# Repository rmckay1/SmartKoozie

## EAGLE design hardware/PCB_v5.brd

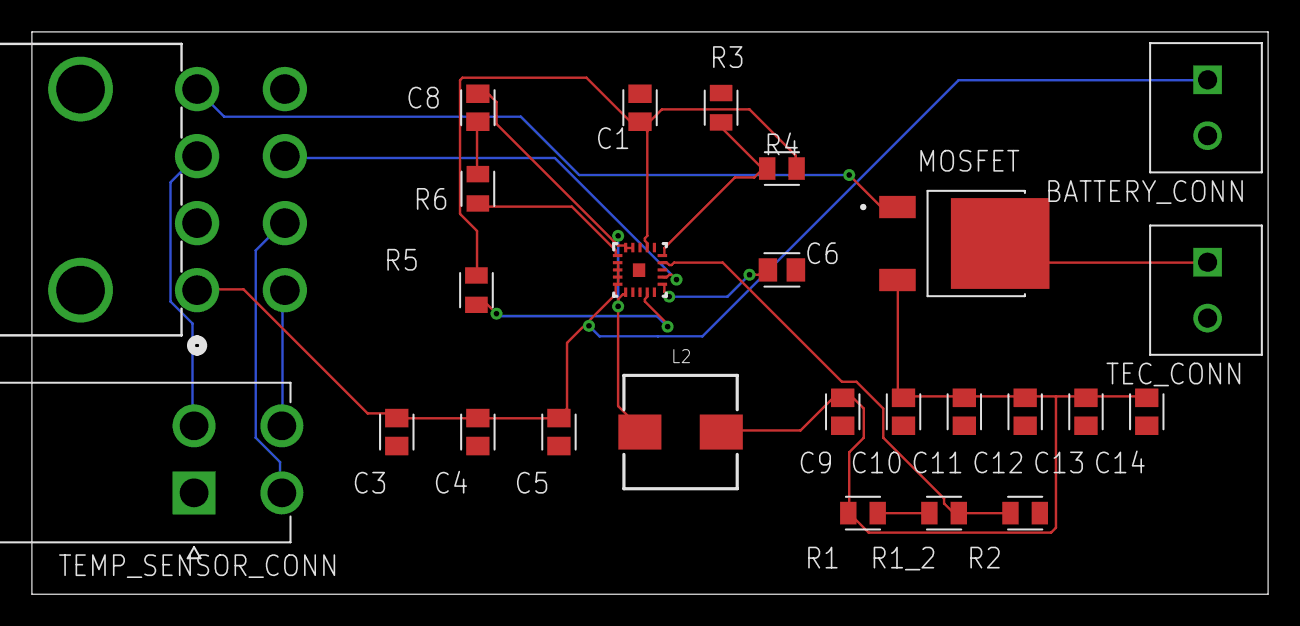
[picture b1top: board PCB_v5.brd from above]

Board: 2 copper layers, 77.4 x 35.2 mm, 26 parts (0 on the bottom side), 18 nets.

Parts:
ARDUINO_CONN: 39301080CONN_5569-08A_MOL; CONN_5569-08A_MOL
BATTERY_CONN: OSTTE020104; OST_OSTTE020104
BUCK_CONVERTER: TPS568230RJERRJE0020A; RJE0020A
C1: 1µF; CAPC2012X110
C3, C4, C10, C11, C12, C13, C14: 22µF; CAPC2012X110
C5, C8, C9: 0.1µF; CAPC2012X110
C6: 22nF; CAPC2012X110
L2: 1.5uF; WE-HCI_7050
MOSFET: TSM340N06CP_ROG; TRANS_TSM340N06CP_ROG
R1: 280k; RESC2012X65
R1_2: 10k; RESC2012X65
R2: 30k; RESC2012X65
R3: 5.1k; RESC2012X65
R4: 330k; RESC2012X65
R5: 100K; RESC2012X65
R6: 0; RESC2012X65
TEC_CONN: OSTTE020104; OST_OSTTE020104
TEMP_SENSOR_CONN: 353180420; MOLEX_353180420

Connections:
5V: ARDUINO_CONN.3, TEMP_SENSOR_CONN.2
COOLER_PWR: MOSFET.2, TEC_CONN.1
EN: ARDUINO_CONN.7, BUCK_CONVERTER.12
GND: ARDUINO_CONN.2, BATTERY_CONN.2, BUCK_CONVERTER.7, BUCK_CONVERTER.8, BUCK_CONVERTER.10, BUCK_CONVERTER.13, BUCK_CONVERTER.16, BUCK_CONVERTER.18, BUCK_CONVERTER.21, C1.2, C3.1, C4.1, C5.1, C6.2, C9.1, C10.1, C11.1, C12.1, C13.1, C14.1, R2.2, R3.1, TEC_CONN.2, TEMP_SENSOR_CONN.1
MODE: BUCK_CONVERTER.15, R3.2, R4.2
unnamed: BUCK_CONVERTER.9, R5.2
unnamed: BUCK_CONVERTER.11, C6.1
unnamed: BUCK_CONVERTER.1, R6.1
unnamed: C8.2, R6.2
unnamed: BUCK_CONVERTER.14, R1_2.2, R2.1
unnamed: R1.2, R1_2.1
PWM: ARDUINO_CONN.4, MOSFET.1
SCL: ARDUINO_CONN.5, TEMP_SENSOR_CONN.4
SDA: ARDUINO_CONN.6, TEMP_SENSOR_CONN.3
SW: BUCK_CONVERTER.6, BUCK_CONVERTER.19, BUCK_CONVERTER.20, C8.1, L2.1
VCC: BUCK_CONVERTER.17, C1.1, R4.1, R5.1
VIN: ARDUINO_CONN.1, BATTERY_CONN.1, BUCK_CONVERTER.2, BUCK_CONVERTER.3, BUCK_CONVERTER.4, BUCK_CONVERTER.5, C3.2, C4.2, C5.2
VOUT: C9.2, C10.2, C11.2, C12.2, C13.2, C14.2, L2.2, MOSFET.3, R1.1

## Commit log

2025-02-25 Setup
2025-03-13 Create Order Receipts
2025-03-13 added a picture of ordered parts in the hardware folder
2025-03-13 add receipts directory
2025-03-16 Added website folder and website draft
2025-04-02 Starting file of our schematic, created the pins for the Nano
2025-04-02 Created Part forlder for the scheamtic
2025-04-03 created symbol for the mosfet and added it to the schematic
2025-04-03 added the open pins in the schematic for the buck converter
2025-04-08 Removed embedded repo SmartKoozieApp and ignored it
2025-04-08 Moved show_temp folder into firmware
2025-04-08 Moved RemoteXY_V1 folder to firmware folder
2025-04-08 Moved TempSensor folder to firmware folder
2025-04-09 Added a code to test MOSFET with external LED
2025-04-09 Uploaded the final code for Smart Koozie which connects to the Arduino through bluetooth and the user is able to turn on/off cooler from app.
2025-04-10 Updated receipt folder with new receipts
2025-04-10 Changed delay time from 3 secs to 1.5 secs
2025-04-10 Updates some things on the RemoteXY, made it so switch is off by default
2025-04-15 Move Webpage folder to docs
2025-04-15 Exclude docs folder from language stats
2025-04-15 Add files via upload
    Code for IR temperature sensor
2025-04-15 Upload collect data code
2025-04-18 Tried calibratring tmp36 temperature, unsucessful attempt
2025-04-18 Upload some useful drafts useful to build schematic
2025-04-22 Sucessfully calibrated tmp36 temp sensor
2025-04-22 Upload RemoteXY resources
2025-04-24 Remove weird html code
2025-04-24 Clean up
2025-04-24 dont need anymore
2025-04-24 duplicate so get rid of
2025-04-24 Create 3D Model
2025-04-24 rename
2025-04-24 Implemented LEDs to demo
2025-04-24 Starting on file navigation for readme
2025-04-24 added on to the file navigation.md
2025-04-24 added spacing for file navigation
2025-04-24 move the placement of file navigation
2025-04-29 purchased another cooler that is bigger and cheaper
2025-05-06 bought a 40mm x 40mm x 20mm heat sink and added to excel sheet
2025-05-08 Create LICENSE
2025-05-08 Move license to docs folder
2025-05-08 sent the correct poster we created for our presentation
2025-05-08 added datasheets
2025-05-13 Ran a test for checking a can with insulation and without to show the value of insulation around the can
2025-05-13 Create FinalProjectCode
2025-05-13 Rename FinalProjectCode to FinalProjectCode.ino
2025-05-14 Update purchase totals excel
2025-05-14 Upload final purchase totals
2025-05-14 Upload purchase totals

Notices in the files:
parts and their libraries:
COPYRIGHT: Copyright (C) 2025 Ultra Librarian. All rights reserved.
